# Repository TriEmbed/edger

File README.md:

# Edger
Edger is a standalone system for developing for and using the combination of a WIFI-capable ESP32 and one or more Renesas/Dialog mixed signal FPGA chips or peripheral development boards and breakout boards having I2C interfaces. The Renesas/ForgeFPGA synthesis tool used to create FPGA images has a drag and drop GUI that involves zero Verilog or VHDL. It has a built in simulator and generates files that Edger can program in place in the user's system for simple FPGA applications. These FPGAs are around one to two dollars in single quantity, even ones mounted on a DIP board that can plug into a wireless breadboard. Edger is aimed at making FPGAs available to "the rest of us" while also creating a development ecosystem to augment the Espressif IDF and Arduino IDE.

Actually that's how it started, but it has since evolved into a more generic system for communication between a web browser and a network-connected MCU or SBC.
The first device supported is the ESP32.

## Components
The major components of Edger are:

### ant
Ant is the software that runs on the embedded device and provides REST-based access to device features like GPIO pins, I2C buses, etc.

### aardvark
Aardvark is a web interface based on VUE.js that allows for discovering and communicating with boards running Ant.  

### the edger API
The general concept for the edger API is as follows:
* There is an endpoint for each type of functionality (e.g. /api/v1/i2c, /api/v1/gpio)
* These endpoints are accessed via HTTP PATCH verb
* The request payload is transmitted as one or more GET parameters, which:
  * each have the form verb={"param1":"value1", "param2":"value2", ...}
  * different verbs expect different parameters
    * some verbs don't expect parameters but still must terminate with '=', e.g. /api/v1/i2c?scan=
  * can be chained and will be processed in order for more complex functionality
  * return their output as JSON

## Development install
A full Edger development environment allows for development of both ant and aardvark.  Therefore it includes the following components:
* a clone of this Edger git repo
* the Espressif IoT Development Framework (ESP-IDF) for building ant
* node.js and pnpm for building aardvark, and optionally serving it in development mode for debugging
* some scripts and Desktop icons to wrapper and expose the above functionality

A convenience script is provided for installation on (currently Ubuntu) Linux - linux_install.sh
This script does the following:
1. Checks/clones the Edger repo (by default in $HOME/workspace/esp32/edger, or as specified by --with-edger={absolute-path})
2. Checks/clones the ESP IDF (by default in $HOME/esp/esp-idf, or as specified by --with-esp-idf={absolute-path})
3. Installs node.js using the Node Version Manager script - nvm.sh
4. Uses Node Package Manager (npm) to install pnpm
5. Uses pnpm to build aardvark
6. Installs the ESP-IDF (creates $HOME/.espressif)
7. Copies scripts to $HOME/bin:
  * changewifi - accepts input for wifi SSID and password, modifies the ant sdkconfig, and runs idf.py to build (and flash) ant
  * startaardvark - starts the node development server serving up the aardvark page/code
8. (if $HOME/Desktop exists, indicating a graphical interface is installed) Copies Desktop files to create clickable icons:
  * CHANGE WIFI - runs the change wifi script
  * START AARDVARK - runs the startaardvark script
  * START BROWSER - opens the default browser to the local aardvark URL
9. Appends to ~/.bashrc if it's not there already:
  * append $HOME/bin to PATH
  * alias for idf.py that will load the idf exports before running it
  * env variables settings for NVM

## User group
The user group kickoff meeting was held on 8/31/2022. Video here: https://youtu.be/zqejgwW3aIo

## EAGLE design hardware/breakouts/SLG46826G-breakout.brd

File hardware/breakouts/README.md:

# breakouts
Edger project breakout board design files
## SLG46826G breakout for the TSOP-20 package part

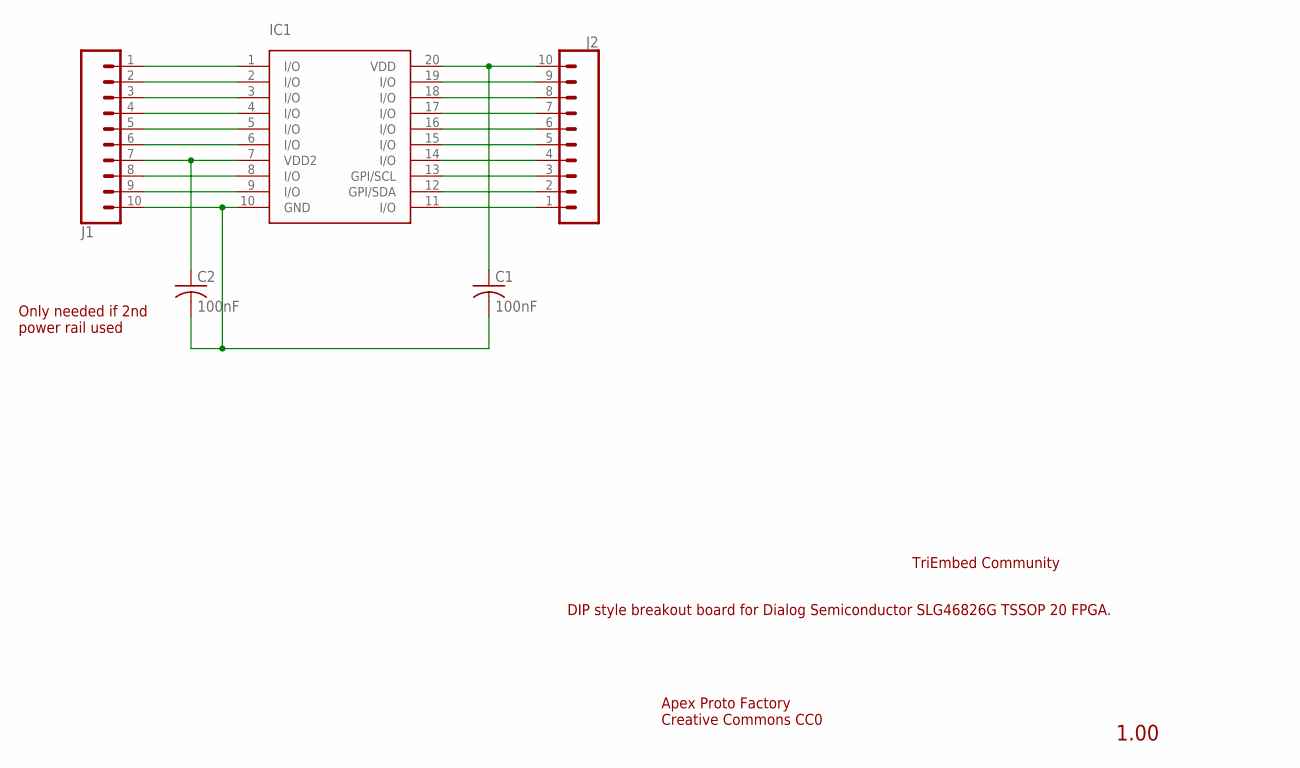
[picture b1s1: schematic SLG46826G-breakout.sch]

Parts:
C1, C2: 100nF; C0805
IC1: SLG46826G; TSOP-20
J1, J2: CONN_10"; 1X10

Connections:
unnamed: IC1.1 (I/O), J1.1
unnamed: IC1.11 (I/O), J2.1
unnamed: IC1.14 (I/O), J2.4
unnamed: IC1.2 (I/O), J1.2
unnamed: IC1.3 (I/O), J1.3
unnamed: IC1.4 (I/O), J1.4
unnamed: IC1.5 (I/O), J1.5
unnamed: IC1.6 (I/O), J1.6
unnamed: C2.1, IC1.7 (VDD2), J1.7
unnamed: IC1.8 (I/O), J1.8
unnamed: IC1.9 (I/O), J1.9
unnamed: C1.2, C2.2, IC1.10 (GND), J1.10
unnamed: C1.1, IC1.20 (VDD), J2.10
unnamed: IC1.19 (I/O), J2.9
unnamed: IC1.18 (I/O), J2.8
unnamed: IC1.17 (I/O), J2.7
unnamed: IC1.16 (I/O), J2.6
unnamed: IC1.15 (I/O), J2.5
unnamed: IC1.13 (GPI/SCL), J2.3
unnamed: IC1.12 (GPI/SDA), J2.2

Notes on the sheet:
Only needed if 2nd power rail used
DIP style breakout board for Dialog Semiconductor SLG46826G TSSOP 20 FPGA.
1.00
TriEmbed Community
Apex Proto Factory Creative Commons CC0

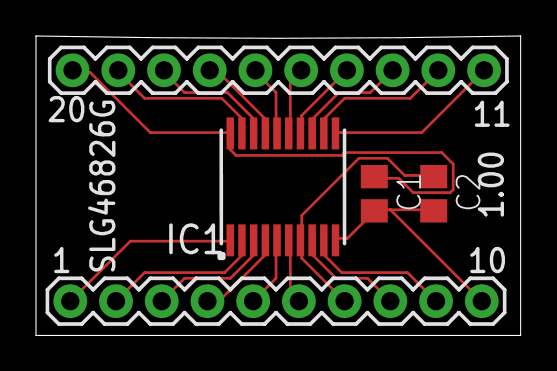
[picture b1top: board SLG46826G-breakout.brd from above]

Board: 2 copper layers, 26.9 x 16.6 mm, 5 parts (0 on the bottom side), 20 nets.

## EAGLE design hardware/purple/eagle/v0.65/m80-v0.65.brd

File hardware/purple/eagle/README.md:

# Hardware CAD and related files for m80 combination Espressif ESP32-C3-M1 (4M) and Dialog SLG47004V-DIP

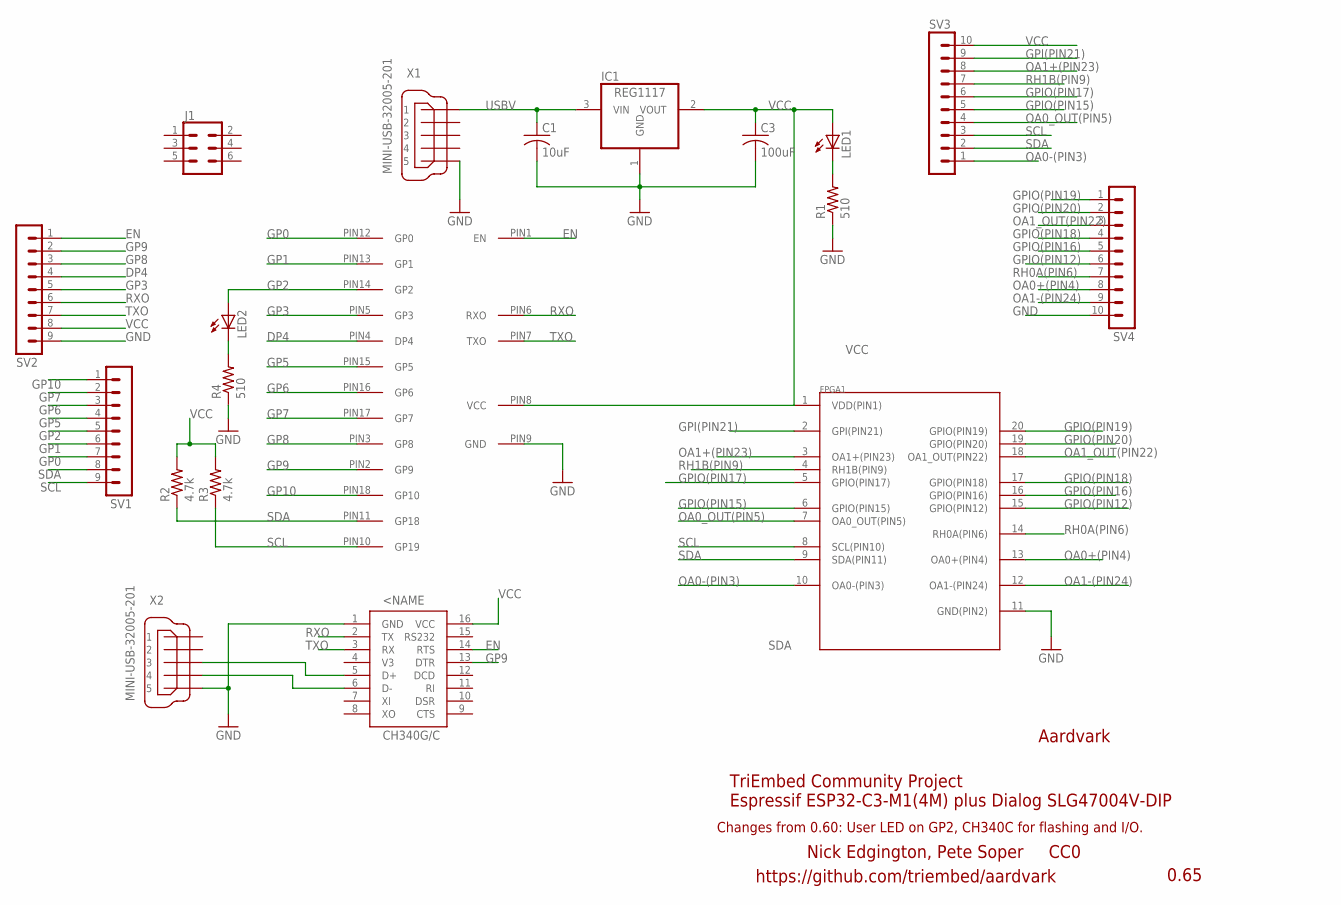
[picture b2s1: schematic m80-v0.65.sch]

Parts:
C1: 10uF; C0805
C3: 100uF; C1206
FPGA1: SLG7004V_DIP; SLG47004V-DIP
IC1: REG1117; SOT223
IC2: CH340G; SOIC16
J1: CONN_03X2NO_SILK; 2X3-NS
LED1, LED2: LEDCHIP-LED0805; CHIP-LED0805
R1, R4: 510; R0805
R2, R3: 4.7k; R0805
SV1, SV2: MA09-1
SV3, SV4: MA10-1
U$2: UNTITLED_ESP32C3; UNTITLED_ESP32-C3-01M
X1, X2: MINI-USB-32005-201; 32005-201

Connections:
DP4: SV2.4, U$2.PIN4 (DP4)
EN: IC2.14 (RTS), SV2.1, U$2.PIN1 (EN)
GND: C1.2, C3.2, FPGA1.11 (GND(PIN2)), IC1.1 (GND), IC2.1 (GND), R1.1, R4.1, SV2.9, SV4.10, U$2.PIN9 (GND), X1.5, X2.5
GP0: SV1.7, U$2.PIN12 (GP0)
GP1: SV1.6, U$2.PIN13 (GP1)
GP2: LED2.A, SV1.5, U$2.PIN14 (GP2)
GP3: SV2.5, U$2.PIN5 (GP3)
GP5: SV1.4, U$2.PIN15 (GP5)
GP6: SV1.3, U$2.PIN16 (GP6)
GP7: SV1.2, U$2.PIN17 (GP7)
GP8: SV2.3, U$2.PIN3 (GP8)
GP9: IC2.13 (DTR), SV2.2, U$2.PIN2 (GP9)
GP10: SV1.1, U$2.PIN18 (GP10)
GPI(PIN21): FPGA1.2 (GPI(PIN21)), SV3.9
GPIO(PIN12): FPGA1.15 (GPIO(PIN12)), SV4.6
GPIO(PIN15): FPGA1.6 (GPIO(PIN15)), SV3.5
GPIO(PIN16): FPGA1.16 (GPIO(PIN16)), SV4.5
GPIO(PIN17): FPGA1.5 (GPIO(PIN17)), SV3.6
GPIO(PIN18): FPGA1.17 (GPIO(PIN18)), SV4.4
GPIO(PIN19): FPGA1.20 (GPIO(PIN19)), SV4.1
GPIO(PIN20): FPGA1.19 (GPIO(PIN20)), SV4.2
unnamed: LED2.C, R4.2
unnamed: IC2.6 (D-), X2.4
unnamed: LED1.C, R1.2
unnamed: IC2.5 (D+), X2.3
OA0+(PIN4): FPGA1.13 (OA0+(PIN4)), SV4.8
OA0-(PIN3): FPGA1.10 (OA0-(PIN3)), SV3.1
OA0_OUT(PIN5): FPGA1.7 (OA0_OUT(PIN5)), SV3.4
OA1+(PIN23): FPGA1.3 (OA1+(PIN23)), SV3.8
OA1-(PIN24): FPGA1.12 (OA1-(PIN24)), SV4.9
OA1_OUT(PIN22): FPGA1.18 (OA1_OUT(PIN22)), SV4.3
RH0A(PIN6): FPGA1.14 (RH0A(PIN6)), SV4.7
RH1B(PIN9): FPGA1.4 (RH1B(PIN9)), SV3.7
RXO: IC2.2 (TX), SV2.6, U$2.PIN6 (RXO)
SCL: FPGA1.8 (SCL(PIN10)), R3.1, SV1.9, SV3.3, U$2.PIN10 (GP19)
SDA: FPGA1.9 (SDA(PIN11)), R2.1, SV1.8, SV3.2, U$2.PIN11 (GP18)
TXO: IC2.3 (RX), SV2.7, U$2.PIN7 (TXO)
USBV: C1.1, IC1.3 (VIN), X1.1
VCC: C3.1, FPGA1.1 (VDD(PIN1)), IC1.2 (VOUT), IC2.16 (VCC), LED1.A, R2.2, R3.2, SV2.8, SV3.10, U$2.PIN8 (VCC)

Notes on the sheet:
0.65
Aardvark
TriEmbed Community Project Espressif ESP32-C3-M1(4M) plus Dialog SLG47004V-DIP
Nick Edgington, Pete Soper CC0
https://github.com/triembed/aardvark
Changes from 0.60: User LED on GP2, CH340C for flashing and I/O.

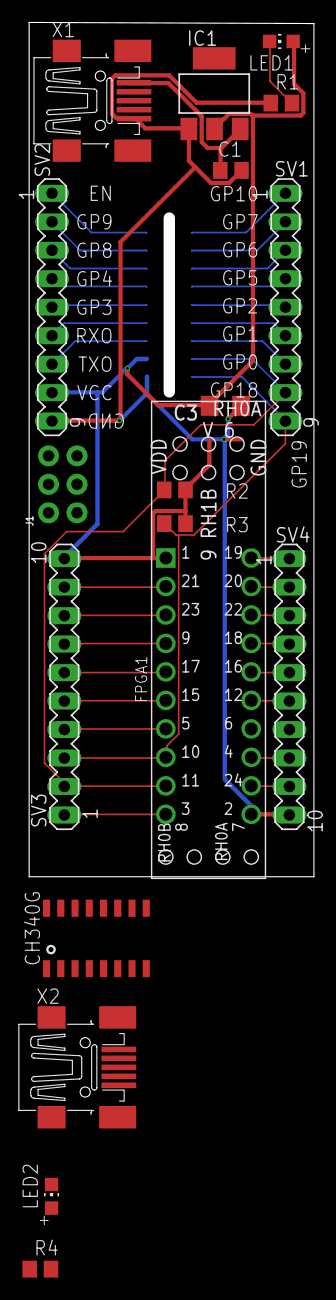
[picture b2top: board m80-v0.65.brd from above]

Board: 2 copper layers, 25.4 x 76.2 mm, 19 parts (0 on the bottom side), 39 nets.

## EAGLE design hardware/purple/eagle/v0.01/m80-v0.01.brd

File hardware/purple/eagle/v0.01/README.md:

# This is version 0.01 that was never implemented

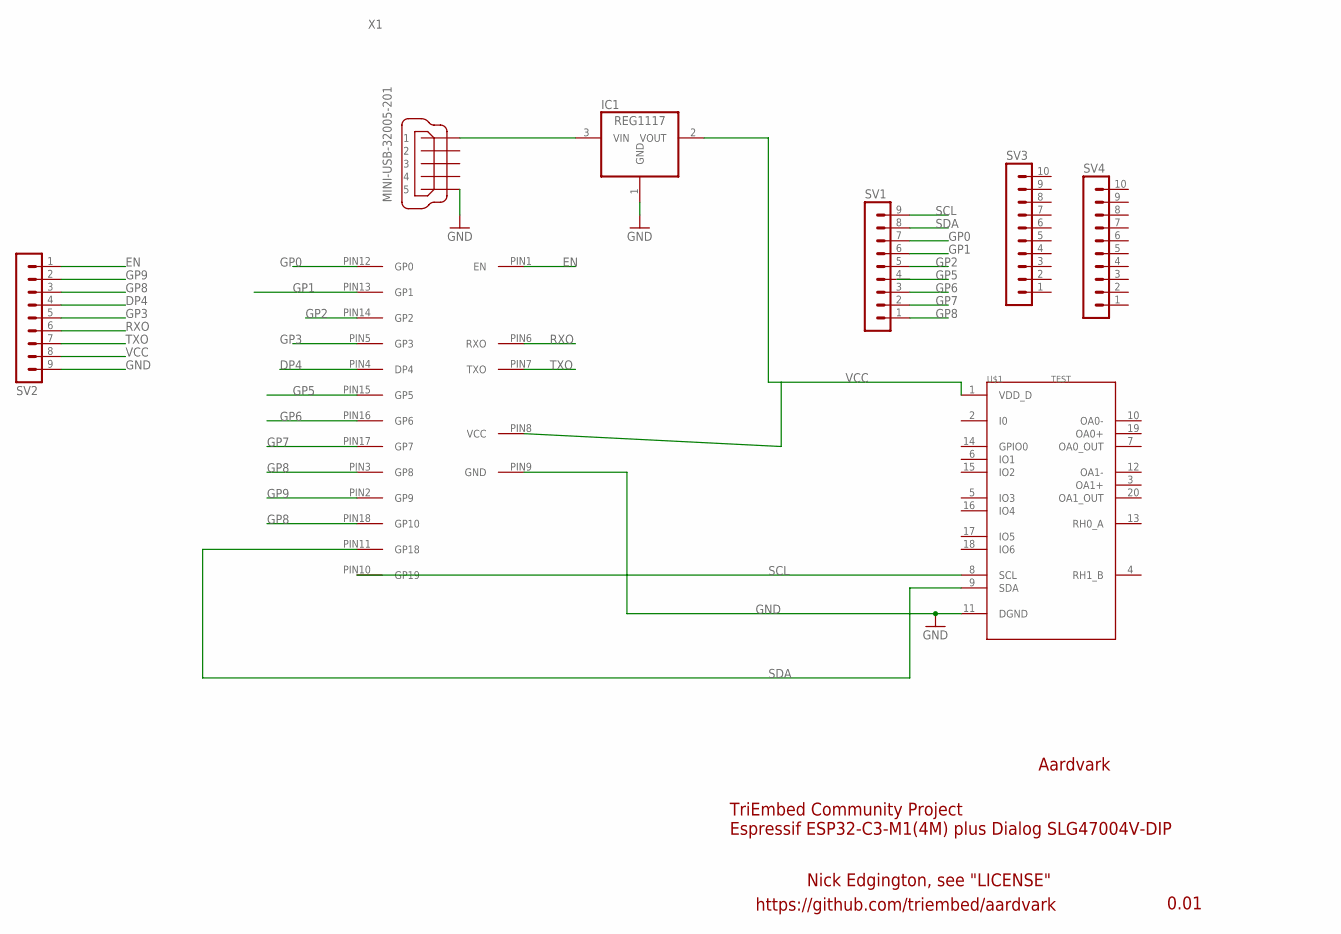
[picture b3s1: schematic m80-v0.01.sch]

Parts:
IC1: REG1117; SOT223
SV1, SV2: MA09-1
SV3, SV4: MA10-1
U$1: TEST; 3M_220-3342-00-0602J_0
U$2: ESP32C3; ESP32-C3-01M
X1: MINI-USB-32005-201; 32005-201

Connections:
DP4: SV2.4, U$2.PIN4 (DP4)
EN: SV2.1, U$2.PIN1 (EN)
GND: IC1.1 (GND), SV2.9, U$1.11 (DGND), U$2.PIN9 (GND), X1.5
GP0: SV1.7, U$2.PIN12 (GP0)
GP1: SV1.6, U$2.PIN13 (GP1)
GP2: SV1.5, U$2.PIN14 (GP2)
GP3: SV2.5, U$2.PIN5 (GP3)
GP5: SV1.4, U$2.PIN15 (GP5)
GP6: SV1.3, U$2.PIN16 (GP6)
GP7: SV1.2, U$2.PIN17 (GP7)
GP8: SV1.1, SV2.3, U$2.PIN3 (GP8), U$2.PIN18 (GP10)
GP9: SV2.2, U$2.PIN2 (GP9)
unnamed: IC1.3 (VIN), X1.1
RXO: SV2.6, U$2.PIN6 (RXO)
SCL: SV1.9, U$1.8 (SCL), U$2.PIN10 (GP19)
SDA: SV1.8, U$1.9 (SDA), U$2.PIN11 (GP18)
TXO: SV2.7, U$2.PIN7 (TXO)
VCC: IC1.2 (VOUT), SV2.8, U$1.1 (VDD_D), U$2.PIN8 (VCC)

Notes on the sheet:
0.01
Aardvark
TriEmbed Community Project Espressif ESP32-C3-M1(4M) plus Dialog SLG47004V-DIP
Nick Edgington, see "LICENSE"
https://github.com/triembed/aardvark

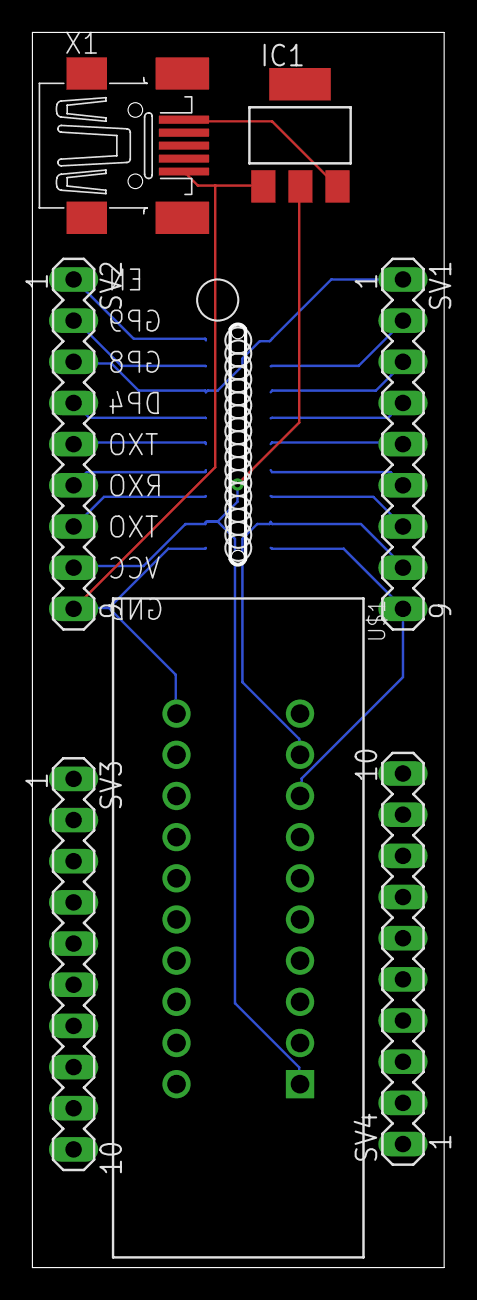
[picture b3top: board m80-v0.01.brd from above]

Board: 2 copper layers, 25.4 x 76.2 mm, 8 parts (0 on the bottom side), 18 nets.

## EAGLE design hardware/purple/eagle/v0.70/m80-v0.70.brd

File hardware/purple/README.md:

# Edger purple standalone ESP32/FPGA board ('cause OSH Park PCBs are purple)

## purple: Making Dialog Semiconductor mixed signal FPGA chips more accessible

v1.00: Stretch of 0.70
Requirements:

Purple 1.00 requirements

To demonstrate a Renesas FORGEFpga (formerly Dialog Greenpak formerly Sylogics) chip application, the 1.00 purple board will feature an FPGA chip to provide the 3.3v rail for the board, assuming there is no thermal constraint prevenging this. The QFN package will be on a daughter board that attaches to the purple board. The LM1117MPX-3.3/NOPB chip, it's inductor and caps and other passives will be on the daugherboard and this will be manufactured in bulk and made as close to freely available as possible so we can stick to the "can be hand-soldered" big rule as much as possible. an alternative strategy would be to have the component footprints for the current .5A regulator cicuit on the board and just have two schemes for assembly: one for hand-soldering using the linear reg and the other for reflow using the FPGA switching reg.

1. Mini->C USB connector if the support parts for C not onerous. NOTE that the board to host USB connection has to be to >= USB rev X to get more than 500mA (vanilla 3 or greater?)
2. Test points to make hand-soldering USB connector easier (MADE MOOT by the presence of a QFN on the board: very few people can hand solder the board if it has a fine-pitch QFN)
3. Small JTAG connector for use with ESP-PROG or the like P L U S separate USB-micro socket for the USB serial JTAG interface to the C3. It isn't clear yet (and would make a wonderful issue for somebody to research) whether or not there is any advantage to the board having the two flavors of JTAG interface. For more details see here: https://docs.espressif.com/projects/esp-idf/en/latest/esp32c3/api-guides/jtag-debugging/index.html
4. Test 0.70 SMD adapter
5. Bring all 20 SMD adapter pins out to male headers
6. Thoroughly test reset and boot circuits with 0.70 + breadboard parts (i.e. partially depopulate and tie bodge wires to male header pins on breadboard)
7. Widen the board for more silkscreen room. Just one row of breadboard positions NO: we will not do this initially
8. Add Digilent Pmod (AMP MODUL MTE) eight position I2C connector. No support for 6/12pos Pmod connectors, only I2C for now.
8. Provide conditioned 5v rail, (4, 8?) channel I2C compatible level shifter. This will further lengthen the board
9. Tesselated C3 module, not the one that fits in a slot. (Still AI-Thinker or Expressif? Dawn?)
10. Power switch between VBUS and rest of board
11. Conditioned VBUS available as 5V source
12. 500mA supply for ESP32 or more if its datasheet calls for it as worst case and we have USB C with its higher current support.
13. Supply regulator must not burn finger at max current (finger guard?). Made moot by use of FORGEFpga regulator circuit (watch the current loop design!)
14. Settle on power and user LEDs NO: we will not do this as the tesselated module has beaucoup pins
16. Jumper to disable user LED
15. Dependency on decent 830 position solderless breadboard or else board is "insert only" and inexperienced people will not be able to get board out of breadboard without breaking a trace, breaking the board, bending pins, etc. Recommend Global Specialties or Twin Industries. This is a simple fact of life because of the large number of pins. You get what you pay for. We should be careful about provenance wrt breadboards we source.
16. Add footprint for FORGEFpga breakout straddling current linear regulator circuit.

1. A stand alone, easy to use Espressif ESP32 C3-based dev board that can be a programmer for the Dialog SLGxxxxx ICs and also run applications with an onboard SLG47004V-DIP.
2. Cache of Dialog info resources
   1. Only resources specifically relevant to the board design and application
   2. Local copies of frequently used docs
   3. Additional cookbooks for getting to blinky with Dialog FPGAs 

This board series is designed in concert with Nick Edgington's "aardvark" node.js web application and the "ant" ESP32 firmware. The ant firmware is designed to allow the ESP32 to directly program a Dialog FPGA without the need for the synthesis tool. This allows change of FPGA personality under programmatic control. An I2C expansion connector allows bus connection of additional FPGAs.

## Project Status

Purple versions 0.60 and 0.70 were released and are still in a testing phase. The board silkscreen labels the boards with the name "Aardvark". This will change with future versions.

A version 1.00 board is being planned for TBD release with the following changes:
1. Name change to "TBD"
2. ECO elimination
3. Updates to reset and boot circuitry
4. Provision for a strap to tie the USB connector down and reduce the chance of broken solder joints.
5. Considering connection of SMD adapter pins to Dialog DIP pins if a compatible set of connections can be worked out. This would allow an SMD part in the adapter to be used for in circuit testing and not just programming.

### Release notes

**0.70** 2/11/2022 - Second prototype. Pure superset of 0.60:

1. Set of female headers to accept a Dialog programming adapter. The adapter and the SLG4704V-DIP cannot be on the board at the same time.
2. CH340C USB interface chip that obviates the need for a dongle for programming via USB.
3. User-controlled LED connected to GPIO2 (pin 14?)
4. Reset pushbutton with a 4.7uF cap across it to stretch time it takes enable to return to a high level
5. Aluminum electrolytic cap for regulator output
6. Four position header for connecting ESP32's I2C bus to an outboard Dialog chip for programming. 
7. C3 module firmware creating access point to provide a wireless web interface for fetching FPGA images from the aarvark application.
8. Shorter and narrower slot for C3 board to fit more tightly
9. Dialog board cannot be plugged in backwards
10. There is a SEVERE issue with mechanical integrity of solder joints with the mini-USB connector on the board. Numerous fractured joints have taken place with normal usage. 

**0.60 Initial prototype 1/24/2022

1. 3.3v regulated supply with power on LED, 
2. AI Thinker ESP32-C3-M1 single RISCV core + WIFI + Bluetooth
3. Socket for Dialog SLG47004V-DIP for programming purposes and/or to combine with the ESP32 for applications
4. Requires USB to serial logic cable with both RTS and DTR control for programming
5. Designed to work with firmware that makes the system a general purpose Dialog chip programmer

## Bug/Todo/Wish Lists

   Note: Many items become easy when we can go with a MUCH larger board that follows the big rule of providing a generous area for people to put their own circuitry in place in a straight forward manner. But this requires a supplier other than OSH Park for significantly lower cost. Guestimate can switch to cheaper supplier for rev 0.80 assuming no major problems with 0.70. So with this in mind expect the "wish" items to become "todo" with the larger board.
   "*" means fixed/implemented for next release (in next rev Eagle files) 
   "^" means item to be fixed/implemented when board size increased

### Version 0.80 Bug/Todo/wish list.

1. Thorough design review(s)
2. Switch to USB micro connector? This needs group discussion. There is an inexpensive supply of USB mini sockets in hand while getting inexpensive micros is on the wrong side of Chinese New Year. Need to hash this out for version 0.80.
2. Bug: Silkscreen hard to read. Need booth library and board layout changes.
3. Wish: Silkscreen should include SLG47004V-DIP pin labels, not just numbers.
4. Todo: Need pushbutton for boot? 
5. Todo: Provision for additional Dialog chips?
6. Wish: Pet peripheral footprints
7. Bug: No consensus about licensing. 0.70 board has "CC By-SA 2.00" on underside but we need concensus for 0.80 as it will be released to the public unless it requires a lot of bodge wires. 
8. Relocate female headers to prevent interference between DIP board and C3 module.

### Version 0.70 bug/todo list: 

1. Bug: Decoupling/bypass cap for CH340C overlooked: 100nF cap has to be added on top of the USB chip manually as part of assembly.
2. Todo: The reset circuit is incomplete. Have to cut the traces from !DTR (pin 14) and !RTS (pin 13) under the chip them through a pair of NPN resistors to EN and GP9. A boot switch will be added by gluing it to the board.
3. DIP board comes too close to C3 module, requiring a notch to be cut into the edge of the DIP board.

### Version 0.60 Bug/Todo/wish list.

1. *U G H  B U G: Not clear which way to plug in the SLG47004V-DIP. Plugging it in backwards might be very bad. Make it physically impossible to plug the board in backwards. Arranging for interference with the C3 or other tall part if backwards should make this relatively trivial to do. REMEMBER the board footprint has to be turned 180 degrees to accomplish this. The "long" end of the SLG has to point the other way so the short end can be close to the C3, making it impossible to insert the SLG the wrong way.
2. Bug: No review process for this board version. Could have avoided some mistakes and gotten some ideas for improvement. Let's not send an update to fab without a couple days open for peer review.
3. *Bug: Center to center distance of header pairs off slightly. Need to line up to work well with breadboard. Wish: Consider cutouts to make use of breadboard feasible even when the board is larger such as 10x10cm. Side would be cut out from edge, then have rectangular cutouts along other side for access to the breadboard jumper sites.
4. *Bug: Name on underside of board is misspelled.
5. Bug: No license on silkscreen, only in the Eagle schematic (and that was unilateral: not the will of the FPGA working group.
6. *Bug: Schematic doesn't match build:
    1. Reg output caps 2x68uF but cap used is 100uF
    2. Through hole caps instead of SMD
    3. Pullups not specified resistance

## Parts issues

As of 6/2/2022 most parts are in hand to build about a dozen more que_m80 boards. Notable exception is the pushbutton switches. Hopefully other parts availability improving with the lessening pandemic crisis in China.

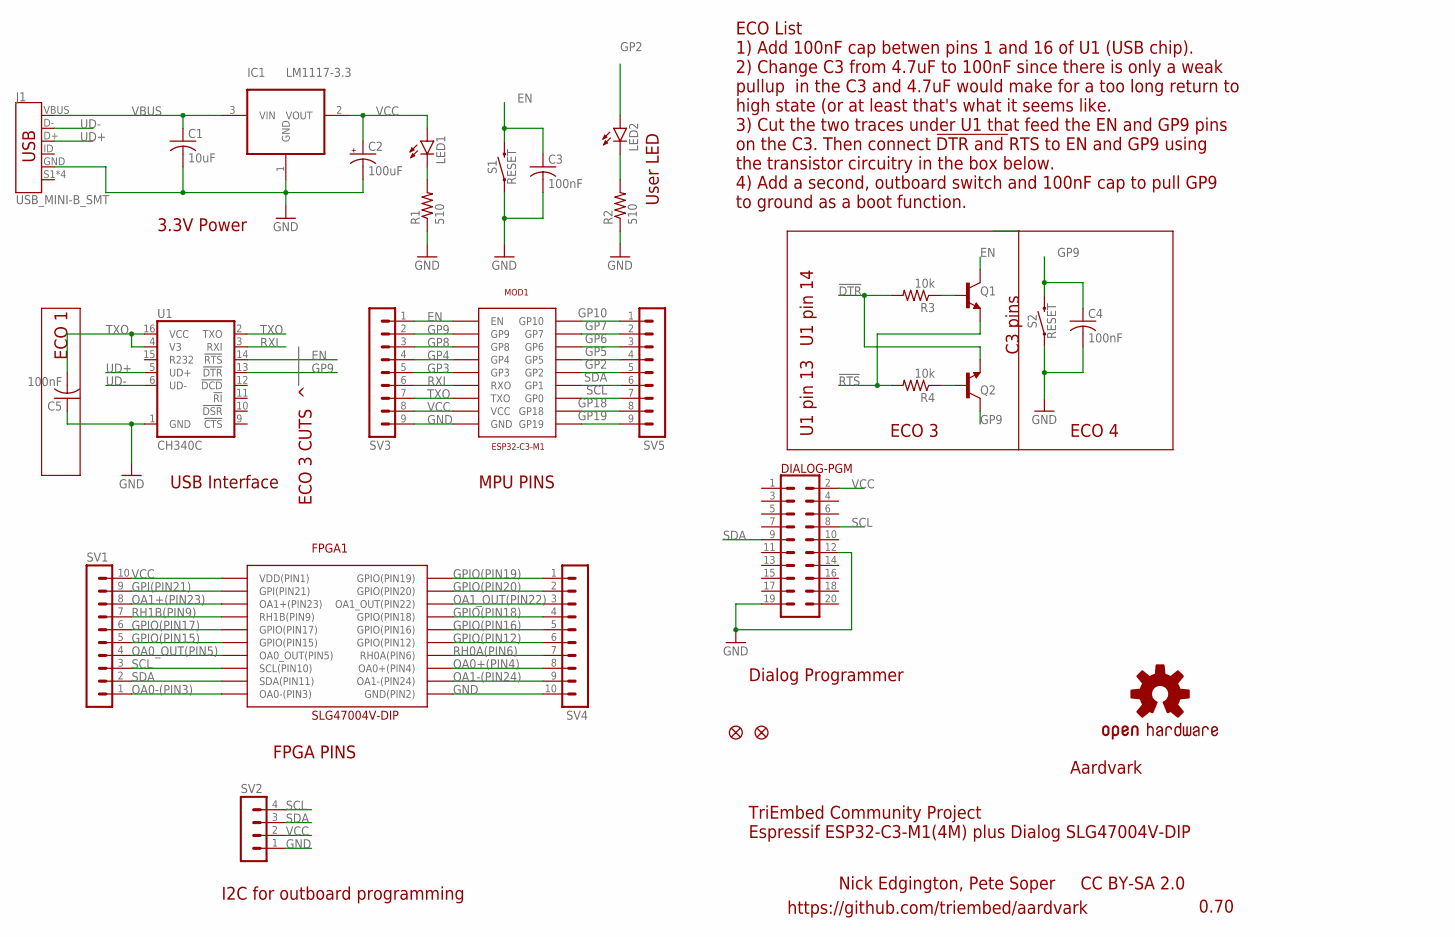
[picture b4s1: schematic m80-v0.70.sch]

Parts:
C1: 10uF; C0805
C2: 100uF; PANASONIC_D
C3, C4, C5: 100nF; C0805
DIALOG-PGM: CONN_10X2; 2X10
FD1, FD2: FIDUCIAL1X2; FIDUCIAL-1X2
FPGA1: SLG47004V-DIP
IC1: LM1117-3.3; SOT223
J1: USB_MINI-B_SMT; USB-MINIB
LED1, LED2: LEDCHIP-LED0805; CHIP-LED0805
LOGO1: OSHW-LOGOMINI; OSHW-LOGO-MINI
MOD1: ESP32-C3-M1; AITHINKER-C3-M1
Q1, Q2: TRANS_NPN-MMBT2222AL; SOT23-3
R1, R2: 510; R0805
R3, R4: 10k; R0805
S1, S2: RESET; TACTILE_SWITCH_SMD_6.0X3.5MM
SV1, SV4: MA10-1
SV2: MA04-1
SV3, SV5: MA09-1
U1: CH340C; SO016

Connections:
!DTR: Q2.2 (E), R3.2
!RTS: Q1.2 (E), R4.2
EN: C3.1, MOD1.PIN1 (EN), Q1.3 (C), S1.2, SV3.1, U1.14 (!RTS)
GND: C1.2, C2.-, C3.2, C4.2, C5.1, DIALOG-PGM.12, DIALOG-PGM.19, FPGA1.11 (GND(PIN2)), IC1.1 (GND), J1.GND, MOD1.PIN9 (GND), R1.1, R2.1, S1.1, S2.1, SV2.1, SV3.9, SV4.10, U1.1 (GND)
GP2: LED2.A, MOD1.PIN14 (GP2), SV5.5
GP3: MOD1.PIN5 (GP3), SV3.5
GP4: MOD1.PIN4 (GP4), SV3.4
GP5: MOD1.PIN15 (GP5), SV5.4
GP6: MOD1.PIN16 (GP6), SV5.3
GP7: MOD1.PIN17 (GP7), SV5.2
GP8: MOD1.PIN3 (GP8), SV3.3
GP9: C4.1, MOD1.PIN2 (GP9), Q2.3 (C), S2.2, SV3.2, U1.13 (!DTR)
GP10: MOD1.PIN18 (GP10), SV5.1
GP18: MOD1.PIN11 (GP18), SV5.8
GP19: MOD1.PIN10 (GP19), SV5.9
GPI(PIN21): FPGA1.2 (GPI(PIN21)), SV1.9
GPIO(PIN12): FPGA1.15 (GPIO(PIN12)), SV4.6
GPIO(PIN15): FPGA1.6 (GPIO(PIN15)), SV1.5
GPIO(PIN16): FPGA1.16 (GPIO(PIN16)), SV4.5
GPIO(PIN17): FPGA1.5 (GPIO(PIN17)), SV1.6
GPIO(PIN18): FPGA1.17 (GPIO(PIN18)), SV4.4
GPIO(PIN19): FPGA1.20 (GPIO(PIN19)), SV4.1
GPIO(PIN20): FPGA1.19 (GPIO(PIN20)), SV4.2
unnamed: LED2.C, R2.2
unnamed: LED1.C, R1.2
unnamed: Q1.1 (B), R3.1
unnamed: Q2.1 (B), R4.1
OA0+(PIN4): FPGA1.13 (OA0+(PIN4)), SV4.8
OA0-(PIN3): FPGA1.10 (OA0-(PIN3)), SV1.1
OA0_OUT(PIN5): FPGA1.7 (OA0_OUT(PIN5)), SV1.4
OA1+(PIN23): FPGA1.3 (OA1+(PIN23)), SV1.8
OA1-(PIN24): FPGA1.12 (OA1-(PIN24)), SV4.9
OA1_OUT(PIN22): FPGA1.18 (OA1_OUT(PIN22)), SV4.3
RH0A(PIN6): FPGA1.14 (RH0A(PIN6)), SV4.7
RH1B(PIN9): FPGA1.4 (RH1B(PIN9)), SV1.7
RXI: MOD1.PIN6 (RXO), SV3.6, U1.3 (RXI)
SCL: DIALOG-PGM.8, FPGA1.8 (SCL(PIN10)), MOD1.PIN12 (GP0), SV1.3, SV2.4, SV5.7
SDA: DIALOG-PGM.9, FPGA1.9 (SDA(PIN11)), MOD1.PIN13 (GP1), SV1.2, SV2.3, SV5.6
TXO: C5.2, MOD1.PIN7 (TXO), SV3.7, U1.2 (TXO), U1.4 (V3), U1.16 (VCC)
UD+: J1.D+, U1.5 (UD+)
UD-: J1.D-, U1.6 (UD-)
VBUS: C1.1, IC1.3 (VIN), J1.VBUS
VCC: C2.+, DIALOG-PGM.2, FPGA1.1 (VDD(PIN1)), IC1.2 (VOUT), LED1.A, MOD1.PIN8 (VCC), SV1.10, SV2.2, SV3.8

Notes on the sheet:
0.70
Aardvark
TriEmbed Community Project Espressif ESP32-C3-M1(4M) plus Dialog SLG47004V-DIP
Nick Edgington, Pete Soper CC BY-SA 2.0
https://github.com/triembed/aardvark
FPGA PINS
MPU PINS
USB Interface
3.3V Power
User LED
Dialog Programmer
I2C for outboard programming
ECO List 1) Add 100nF cap betwen pins 1 and 16 of U1 (USB chip). 2) Change C3 from 4.7uF to 100nF since there is only a weak pullup in the C3 and 4.7uF would make for a too long return to high state (or at least that's what it seems like. 3) Cut the two traces under U1 that feed the EN and GP9 pins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
ECO 3 CUTS ^
U1 pin 13
U1 pin 14
C3 pins
ECO 4
ECO 3
ECO 1

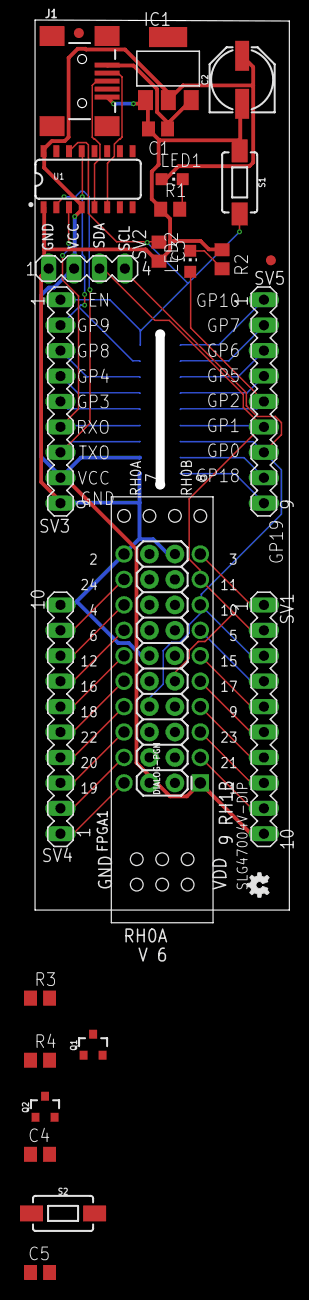
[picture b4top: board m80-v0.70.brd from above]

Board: 2 copper layers, 25.4 x 88.9 mm, 29 parts (0 on the bottom side), 43 nets.

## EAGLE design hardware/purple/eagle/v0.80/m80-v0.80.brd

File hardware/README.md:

# Triangle Embedded Interest Group (TriEmbed) Edger hardware projects
## Purple - Full custom PCB: ESP32C3 + sockets for FORGEFpga 20 pin DIP board or SMD adapter designed for 830 point solderless breadboard. Reflow soldered except for male header pins. Uses a Renesas 46585 or similar FORGEFpga for voltage regulation (and perhaps sequencing)
## White - Combination 830 point solderless breadbord, ESP32 dev board and SLG47004V-DIP FPGA: Just instructions for a do it yourself assembly functionally equivalent to Purple board. No soldering required.
## Green - Future: "Motherboard" for Purple functionality, peripherals, peripheral connectors and large uncommited area. All reflow soldered except optional female headers? 

In the beginning was Sylogics. Then Dialog bought Sylogics. Dialog created the marketing name "GreenPak" for their simple mixed signal FPGAs. Renesas bought Dialog and changed the "GreenPak" name to "FORGEFpga". The documents on the Internet are a mish-mash of old and new names.

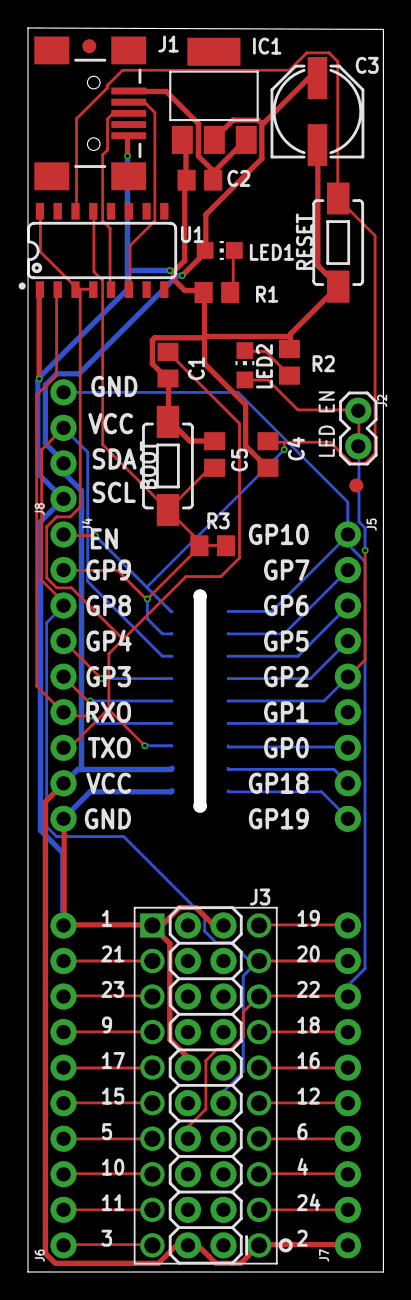
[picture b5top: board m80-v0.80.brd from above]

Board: 2 copper layers, 25.4 x 88.9 mm, 27 parts (1 on the bottom side), 39 nets.

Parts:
BOOT: CK PTS820; TACTILE_SWITCH_SMD_6.0X3.5MM
C1, C5: 100nF; C0805
C2: 10uF 399-6674-1-ND; C0805
C3: 100uF; PANASONIC_D
C4: 2.2uF; C0805
FD1, FD2: FIDUCIAL1X2; FIDUCIAL-1X2
IC1: LM1117-3.3; SOT223
J1: MINI; USB-MINIB
J2: 1X02
J3: 2X10
J4, J5: 1X09_NO_SILK
J6, J7: 1X10_NO_SILK
J8: 1X04_NO_SILK
LED1, LED2: CHIP-LED0805
LOGO1: OSHW-LOGOMINI; OSHW-LOGO-MINI
MOD1: ESP32-C3-M1; AITHINKER-C3-M1
MOD2: SLG47004V-DIP
R1, R2: 510; R0805
R3: 68K; R0805
RESET: CK PTS820; TACTILE_SWITCH_SMD_6.0X3.5MM
U1: CH340C; SO016

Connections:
EN: C4.2, J4.1, MOD1.PIN1, RESET.2, U1.14
GND: BOOT.1, C1.1, C2.2, C3.-, C4.1, C5.1, IC1.1, J1.GND, J3.12, J3.19, J4.9, J6.10, J8.1, MOD1.PIN9, MOD2.1, R1.1, R2.1, RESET.1, U1.1
GP0: J5.7, MOD1.PIN12
GP1: J5.6, MOD1.PIN13
GP2: J2.1, J2.2, J5.5, LED2.A, MOD1.PIN14
GP3: J4.5, MOD1.PIN5
GP4: J4.4, MOD1.PIN4
GP5: J5.4, MOD1.PIN15
GP6: J5.3, MOD1.PIN16
GP7: J5.2, MOD1.PIN17
GP9: BOOT.2, C5.2, J4.2, MOD1.PIN2, R3.1, R3.2, U1.13
GP18: J5.8, MOD1.PIN11
GP19: J5.9, MOD1.PIN10
GPI(PIN21): J7.2, MOD2.12
GPIO(PIN12): J6.6, MOD2.5
GPIO(PIN15): J7.6, MOD2.16
GPIO(PIN16): J6.5, MOD2.6
GPIO(PIN17): J7.5, MOD2.15
GPIO(PIN18): J6.4, MOD2.7
GPIO(PIN19): J6.1, MOD2.10
GPIO(PIN20): J6.2, MOD2.9
unnamed: LED2.C, R2.2
unnamed: LED1.C, R1.2
OA0+(PIN4): J6.8, MOD2.3
OA0-(PIN3): J7.10, MOD2.20
OA0_OUT(PIN5): J7.7, MOD2.17
OA1+(PIN23): J7.3, MOD2.13
OA1-(PIN24): J6.9, MOD2.2
OA1_OUT(PIN22): J6.3, MOD2.8
RH0A(PIN6): J6.7, MOD2.4
RH1B(PIN9): J7.4, MOD2.14
RXI: J4.6, MOD1.PIN6, U1.2
SCL: J3.8, J5.1, J7.8, J8.4, MOD1.PIN18, MOD2.18
SDA: J3.9, J4.3, J7.9, J8.3, MOD1.PIN3, MOD2.19
TXO: C1.2, J4.7, MOD1.PIN7, U1.3, U1.4, U1.16
UD+: J1.D+, U1.5
UD-: J1.D-, U1.6
VBUS: C2.1, IC1.3, J1.VBUS
VCC: C3.+, IC1.2, J3.2, J4.8, J7.1, J8.2, LED1.A, MOD1.PIN8, MOD2.11

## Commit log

2022-09-22 update LICENSE
2022-09-26 updated LICENSE and README.md
2022-10-08 #1 Transmogrified Quercus files
2022-10-08 #1 update README.md
2022-10-16 Update README.md
    #2
2022-10-20 Update README.md
    #2 renumber requirements list
2022-10-20 a few tweaks to purple/eagle/v0.70/BOM.ods (sb copied up and over)
2022-10-27 #3 rearrange hardware/white files into 1.00 and 2.00 directories
2022-10-28 #3 wiring.odt for white board rev 2
2022-10-28 #3 rename hardware/white/1.00, 2.00 to r1, r2
2022-10-28 #3 update hardware/white/README.md
2022-11-05 #3 first pass assembly docuement in hardware/white/r2/wiring.{odt,docx}
2022-11-05 #3 hardware/white/r2/wiring.pdf
2022-11-08 #3 white board r2 assembly updates (not quite done)
2022-11-09 #3 wiring.odt update
2022-11-09 #3 wiring.pdf update
2022-11-09 #3 update wiring.{odt,pdf}
2022-11-11 #3 reorder violet, fix ground to 15 sb 1
2022-11-11 #3 more wiring.{odt,pdf} improvements
2022-11-12 #3 wiring.{odt,pdf} updates
2022-11-16 #3 wiring.{odt,pdf} updates by Dawn Trembath
2022-11-18 #3 hardware/white/r2/wiring.{odt,pdf}
2022-11-18 #3 hardware/white/r2/wiring.{odt,pdf} release candidate
2022-11-18 #3 hardware/white/r2/wiring.{odt,pdf} 1.00 released
2022-11-18 #3 fix resistor placement
2022-11-19 #3 font color wiring.odt
2022-11-19 Add files via upload
    minor formatting tweaks
2022-11-23 #3 Initial refactoring of hardware/white docs
2022-11-25 #2 clean up hardware/white doc
2022-11-25 #2 more doc tidy up
2022-11-25 #3 add hardware/doc/README.md
2022-11-25 #3 fiddling and farting with relative hyperlinks
2022-11-25 #3 more tidy up of hardware files
2022-11-25 #3 hardware doc cleanup
2022-11-25 #3 clean out obsolete doc
2023-01-18 remove obsolete doc/CAD/greenpack-test1.aap
2023-01-18 update blinky app to match with current synth tool
2023-01-18 Added ant, aardvark from (private) nicks_alpha_edger 1/2/2023
2023-01-18 per discussion following All Things Open compatible license change from MIT to GPL 3
2023-01-18 fix esp_vfs_semihost_register call with 2nd parm for v4.4 idf compatibility
2023-01-18 tools/thumbdrive/home/{bin,Desktop} with Desktop icon and script files
2023-01-18 tools/thumbdrive/README.md with instructions
2023-01-18 #5 Update linux_install.sh to reflect overhauled source. This is an untested hack waiting for brave people to try it and Carl to fix it
2023-01-31 #5 update and initial test of linux_install.sh
2023-02-13 #5 more bug fixes to prototype install system
2023-02-13 fix startaardvark pnpm setup
2023-02-13 #5 remove debug exit
2023-02-13 #5 remove debug loop
2023-02-13 #5 hoist package installs
2023-02-13 #5 have to use fresh terminal session if .bashrc edited to add /home/psoper/bin to search rules
2023-02-13 #5 more fixes for desktop icons, scripts, getting pnpm install straight
2023-02-20 #6 Add api directories
2023-02-24 #7 INT trap handler for edgerBMP
2023-03-06 Neaten up, support non-default Ant hostname, include tenths of degrees
2023-03-14 #6 edgerBMP put out both centigrade and fahrenheit
2023-03-18 #6 renamed edgerBMP to edgerBMP85.sh and added Python implementation edgerBMP85.py
2023-03-19 #6 handle exceptions, show one fractional digit
2023-03-19 #6 fix typo, clarify applicability
2023-03-19 #6 cleaned up edgerBMP85.sh
2023-03-19 #6 added edgerBMP3XX.py for BMP388 and BMP390 sensors, updated README.md
2023-04-12 Add files via upload
    Some initial logo drafts
2023-04-12 Add logo files via upload
    edger-logo-v10 has all square shapes
2023-04-12 Add logo files via upload
    v10 has all square shapes
    v11 has a rounded 'O"
2023-04-12 Create README.md for Logo folder
2023-04-25 update top-level README
2023-04-25 README formatting
2023-04-30 incorporate PR comments
2023-04-30 tweaks after reviewing PR commit
2023-05-02 remove \ in front of dollar inside single quotes
2023-05-21 ant install script
2023-05-21 more install changes
2023-05-21 reverse and and aardvark install order
2023-05-21 save args to pass to subinstalls
2023-05-21 add ninja-build back to ant apt
2023-05-21 fix dialout exit case
2023-05-21 trust desktop files and make executable
2023-05-21 disable exit due to dialout group
2023-05-21 copy desktop icon
2023-05-23 changes after talk w/pete
2023-05-23 remove more duplicate actions
2023-05-26 #21 remove ant/.idea
2023-05-26 #21 add temp driver for aardvark ant/main/BMP3XX
2023-05-26 #21 Analog devices ADT7420 temp sensor driver for aardvark graphing function
2023-05-26 #21 HSPPAD143A driver for aardvark accessa
2023-05-26 #21 major updates from Nick
2023-05-26 #21 updated ant/linux_install.sh comments
2023-05-27 add apt-get update
2023-05-28 #19 put 2nd paramter to esp_vfs_semihost_register back: problem was a corrupt repo
2023-05-28 comment usb.getDevices from Home view
2023-05-29 comment testEvent() instead of usb section of the function
2023-05-29 disable interfaces
2023-05-29 disable project list
2023-05-29 disable gpio blinky, i2c edit, Renesas BuzyBox in ant
2023-05-29 try dynamic broken hide
2023-06-03 aardvark install updates
2023-06-07 dynamic show hidden menus
2023-06-08 change flat and readonly to real booleans per errors
2023-06-08 fix error from using this in function defined with =>
2023-06-08 resolve null routes error
2023-06-08 hide broken menus instead of disabling
2023-06-08 #21 prevent null access error with js out of dist
2023-06-24 use dev mode for build
2023-06-28 #29 kill spinner, extra menus, bad caching
2023-06-28 #15 build a dist directory that can be accessed directly by a web brower
2023-06-28 #15 add missing VueIp.vue
2023-06-28 #15 fix program name
2023-06-29 .env changes for name and github link
2023-06-29 rename scan button
2023-06-29 use vuetify color-picker
2023-06-29 change loading-text on main data table
2023-06-30 init led to match ant
2023-08-03 console feature starting bleedingedge branch
2023-09-11 change idfexport function to idf.py alias
2023-09-14 temp file tools/foo
2023-09-14 #27 update version number in aardvark ui
2023-09-18 tell the browser to not cache aardvark traffic
2023-09-18 #29 change rev string to 0.1.1
2023-09-18 #29 tell browsers to not cache pages (0.1.1)
2024-03-09 Update esp.js
    #29 Aardvark esp.js missing no-cache header item
2024-03-09 Update esp.js
    #29 Add missing header item to suppress caching

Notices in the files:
parts and their libraries:
SparkFun-Connectors: Licensing: Creative Commons ShareAlike 4.0 International - https://creativecommons.org/licenses/by-sa/4.0
PJS: Author, license:
